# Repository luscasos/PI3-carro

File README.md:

# Projeto integrador III

## Informações gerais
Desenvolvido no escopo da disciplina de Projeto Integrador III, do curso de Eng. Eletrônica do IFSC campus Florianópolis no primeiro semestre de 2019, esse projeto tem como objetivo utilizar os conhecimentos obtidos ao decorrer do curso, implementando um carro controlado via aplicativo Android.

## Tabela inicial de requisitos
* Controle via aplicativo Android
* Comunicação via bluetooth
* Sensoriamento de velocidade e transmissão para o app 
* Controle de velocidade via aplicativo 
* Controle da bateria

## Tecnologias
* Parte mecânica do carro, disponível em https://s.click.aliexpress.com/e/bD9t0zL3
* Celular Android
* Microcontrolador STM32
* Bateria de íon de lítio
	
# Hardware

* ## Acionamento dos motores

Para acionar os motores foram levadas em conta os requisitos de projeto, que nesse quesito são:
* Controle de direção do movimento
* Controle de velocidade

Com relação ao controle de direção foi escolhido o sistema de ponte H, na qual é possível alterar o sentido da corrente invertendo as tensões nos terminais L e R, a forma escolhida de acionamento dos motores foi conectar em paralelo os motores do mesmo lado do carro, necessitando de duas pontes para o controle dos quatro motores 

O primeiro filtro para escolha do circuito foi a disponibilidade de componentes no almoxarifado, que para ponte H se limitava a:
* L293B
Corrente máxima 1A por canal

* L6203		
Corrente máxima 5A

* SN754410NE
Com uso restrito para manutenção

* Circuito discreto com BD140 e BD139
Corrente máxima 1,5A
 
### Escolha
Como nesse projeto vamos trabalhar com quatro motores, dois por canal, e sendo eles de tensão nominal de 3 - 6V e corrente nominal de 300mA todos os circuitos cumprem o requisito de potência mínima, O L6203 foi descartado por ser uma ponte H de potência, ficando superdimensionado e encarecendo o projeto, ficando a escolha entre o circuito discreto e o L2931B no quesito eficiência energética, afinal, se trata de um sistema embarcado, e por isso necessita de um cuidado maior com a eficiência
Montado os dois circuitos de acionamento alimentados em 5V foi obtido uma tensão de 3,08V com o integrado e 4,6V no circuito discreto, uma diferença de 35% no consumo do circuito, sendo escolhido o circuito discreto.  

Circuito final de alimentação dos motores, com queda de 0,4V de tensão na carga em relação a VCC e corrente de polarização externa de 640pA, não exigindo muita corrente do microcontrolador.

* ## Microcontrolador
Para controle do carro foi utilizado o stm32f103, na sua versão de desenvolvimento conhecido como "blue pill", que possui um cortex M3 com um clock de 72MHz e que conta com 20kb de RAM, quatro Timers, dois ADCs entre outros, que serão usados na aplicação.

* ## Comunicação
Como a comunicação entre celular e carro é feita via bluetooth foi escolhido o modulo HC-05, que trata todo o protocolo de comunicação e se comunica com microcontrolador via UART, sendo de fácil uso e configuração.

* ## Aferição de velocidade 
Para medir a velocidade foi escolhido um encoder com sensor óptico, que consiste em um diodo emissor de luz e um receptor, separados por uma roda perfurada, que quando a roda esta em movimento gera um sinal com frequência proporcional a velocidade da roda.

* ## Baterias 
Para alimentar o carro foram escolhidas duas baterias de LIPO, de 3,7V e 1200mAh, conectadas em série, o que resulta em 7,4V de tensão. 

* ## Regulador de tensão
Como o conjunto de baterias tem como tensão 7,4V na saída, é necessário baixar a tensão para níveis aceitáveis para o microcontrolador e modulo bluetooth, no caso foi usado um regulador ajustável Step-up-down, por questão de disponibilidade, mesmo esse sendo superdimensionado para a aplicação em questão, já que suporta correntes de até 5A e nesse caso não passa de 200mA.

* ## Medição da tensão das baterias
Como regra geral, não se pode descarregar uma bateria abaixo de uma certa tensão, com as usadas nesse projeto não é diferente, não sendo recomendado baixar a tensão da marca dos 3V, como o sistema possui duas baterias é necessário medir a tensão delas individualmente. O conversor analógico digital do microcontrolador tem como tensão base 3V, então é preciso baixar as tensões para menos de 3V, o circuito usado para isso é o diferencial com ampop, que pode dar um ganho menor que 1, sem usar tensão negativa. O Ampop escolhido foi o LM324, com ganho de 1/3 para a tensão superior (bateria 1 em serie com a bateria 2), e de 2/3 para a tensão media (bateria 1). 

* ## Placa de circuito
Com todos os requisitos de Hardware definidos foi desenvolvido o esquemático e placa do projeto

A placa de circuito impresso foi projetada para que o circuito de comunicação bluetooth ficasse longe do principal foco do ruído do circuito, que são os motores, contudo ainda foi deixado o uC ao lado dos motores e das pontes H, uma implementação mais correta seria distanciar esses dois componentes geradores de ruído, juntamente com o regulador de tensão. e acoplar o sensor de velocidade de outra maneira, que não por cabos longos como foi projetado, essas e outras correções foram feitas em outra placa a ser utilizada em disciplinas ligadas a programação de microcontroladores.

O carro também foi objeto de estudo por uma dupla de colegas dentro da disciplina de compatibilidade eletromagnética, estando todos dados disponíveis no link https://github.com/lsmanoel/CEM_3

# Software do microcontrolador

* ## Controle de velocidade
O controle da velocidade vai ser feito por meio da técnica de modulação PWM, via microcontrolador atuando sobre a ponte H.
Como o circuito de ponte H escolhido não pode em hipótese alguma ter o os dois transistores de atuação polarizados ao mesmo tempo, optou-se por utilizar o PWM no modo normal e no modo inverso, de forma a construir um sistema redundante nesse sentido, se houver uma falha no software mesmo assim não haverá um problema critico na ponte H.

A implementação foi feita via dois Timers, com frequência fixa em 1kHz, em ambos usando o canal 1 e o canal 1N, trabalhando sempre com pelo menos um deles desligado. Sabendo que a velocidade vai ser transmitida pelo aplicativo em 1Byte, com 256 possibilidades, de -128 a 127. Sendo assim o valor 127 corresponde a 100% da velocidade para frente, enquanto -128 corresponde a 100% da velocidade na ré.
Como os motores possuem uma inércia, não será qualquer valor de tensão que dará partida no carro, sabendo disso pode-se dar um offset no valor do pwm, nesse caso escolhi cerca de 45% de razão cíclica, o que é suficiente para dar partida nos motores.

* ## Medição das baterias
A medição das baterias foi feita por um ADC, utilizando dois canais, um para a tensão total (bateria 1 em serie com a bateria 2) e um canal para a tensão da bateria 1, lembrando que estas tensões já receberam um ganho de 1/3 (tensão total) e 2/3 (tensão da bateria 1). então levando em consideração esse ganho e os dois canais pode-se medir individualmente a tensão de cada bateria para que o sistema possa desligar os motores e avisar o usuário que a carga das baterias esta crítica.

* ## Medição da velocidade
A velocidade é calculada com base na variação de um sensor ótico e como a roda perfurada possui 20 furos, para cada uma volta da roda são medidas 20 alternâncias no sensor, com isso e o diâmetro da roda é possível saber a distância percorrida por pulso. Além da componente de distância é necessário saber o tempo entre medições, nesse caso foi utilizada um tempo de 100ms.

onde n é o número de pulsos por período

Também foi implementado um [filtro media movel](http://borgescorporation.blogspot.com/2013/05/filtro-de-media-movel.html
) de 16 fatores afim de filtrar ruídos indesejados

* ## Comunicação
A comunicação entre o microcontrolador e o modulo bluetooth HC-05 é feita via UART que possui hardware dedicado na maioria dos microcontroladores, então a implementação consiste basicamente em criar um pacote de dados para envio de todos os parâmetros juntos no formato "00;00;00;00". O tratamento de dados recebidos pelo uC é feito por interrupção, reconhecendo o final do dado, que é "\r\n" e separando os demais bits, que são as coordenadas Y e Z.

# Controle de Direção e sentido
Tanto o controle de direção quanto o de sentido serão feitas via aplicação em Android e transmitidas por bluetooth para o microcontrolador embarcado no carro, o controle de sentido será feito via dois botões, um para ré e outro para frente, não pressionado nenhum o carro fica parado, com a possibilidade de fixar uma velocidade constante. A direção será feita via medição dos acelerômetros do celular, que fara o celular nesse caso atuar como um volante.

# Aplicativo Android

O aplicativo conta com as seguintes funcionalidades:

* Botão de conexão bluetooth no canto superior direito, que é responsável por ligar o bluetooth caso o mesmo esteja desligado, buscar a lista de dispositivos pareados e conectar no mesmo, iniciando a comunicação.
* Botão Start/Stop responsável por interromper ou não o fluxo de dados de aceleração do celular para o dispositivo pareado.
* Texto central com os valores de aceleração individual dos eixos.
* Texto na lateral esquerda com os valores de bateria e velocidade enviados pelo dispositivo conectado. 

<p>
A estrutura dos dados de aceleração é a seguinte: 
<pre><code>byte dado[]=new byte[4];
        dado[0]=y;
        dado[1]=z;
        dado[2]='\r';
        dado[3]='\n';
        connectedThread.write(dado);
  </code></pre>
</p>

Já a estrutura dos dados recebidos tem que estar no seguinte formato: "00;00;00;00", sendo que o aplicativo insere uma virgula entre cada um dos valores.

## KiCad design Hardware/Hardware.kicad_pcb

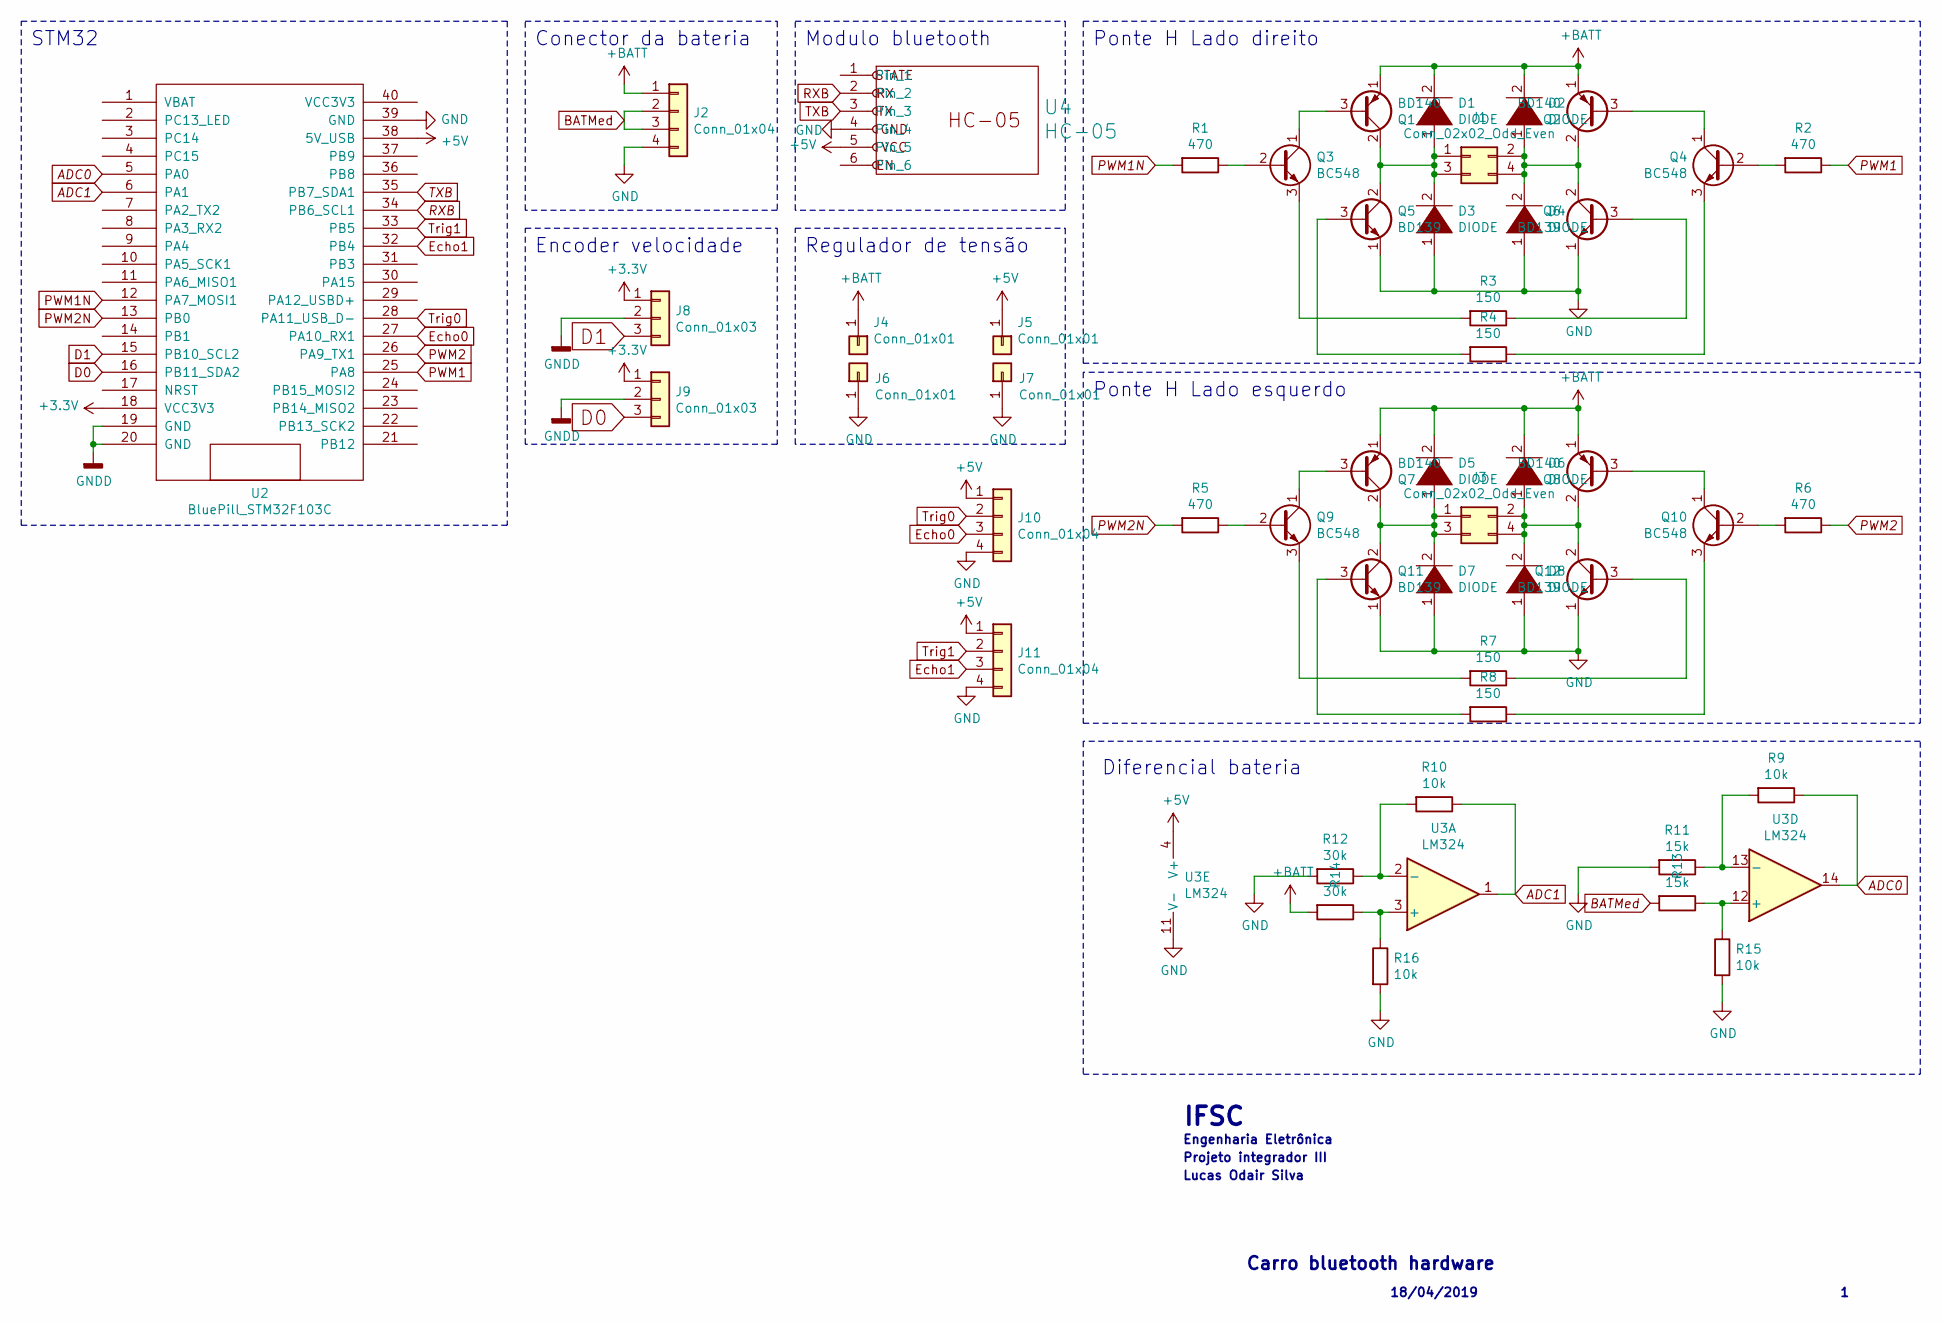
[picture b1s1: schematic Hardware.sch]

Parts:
D1, D2, D3, D4, D5, D6, D7, D8: DIODE; D_A-405_P2.54mm_Vertical_AnodeUp
J1, J3: Conn_02x02_Odd_Even; PinHeader_2x02_P2.54mm_Vertical
J2, J10, J11: Conn_01x04; PinHeader_1x04_P2.54mm_Vertical
J4, J5, J6, J7: Conn_01x01; PinHeader_1x01_P2.54mm_Vertical
J8, J9: Conn_01x03; PinHeader_1x03_P2.54mm_Vertical
Q1, Q2, Q7, Q8: BD140; TO-126-3_Vertical
Q3, Q4, Q9, Q10: BC548; TO-92_Inline
Q5, Q6, Q11, Q12: BD139; TO-126-3_Vertical
R1, R2, R5, R6: 470; R_0805_2012Metric
R3, R4, R7, R8: 150; R_0805_2012Metric
R9, R10, R15, R16: 10k; R_0805_2012Metric
R11, R13: 15k; R_0805_2012Metric
R12, R14: 30k; R_0805_2012Metric
U2: BluePill_STM32F103C
U3: LM324; SOIC-14_3.9x8.7mm_P1.27mm
U4: HC-05; PinHeader_1x06_P2.54mm_Horizontal

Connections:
+3V3: J8.1, J9.1, U2.18 (VCC3V3)
+5V: J5.1, J10.1, J11.1, U2.38 (5V_USB), U3.4 (V+), U4.5
+BATT: D1.2 (A), D2.2 (A), D5.2 (A), D6.2 (A), J2.1, J4.1, Q1.1 (E), Q2.1 (E), Q7.1 (E), Q8.1 (E), R14.2
ADC0: R9.1, U2.5 (PA0), U3.14
ADC1: R10.1, U2.6 (PA1), U3.1
BATMed: J2.2, J2.3, R13.2
D0: J9.3, U2.16 (PB11_SDA2)
D1: J8.3, U2.15 (PB10_SCL2)
Echo0: J10.3, U2.27 (PA10_RX1)
Echo1: J11.3, U2.32 (PB4)
GND: D3.1 (K), D4.1 (K), D7.1 (K), D8.1 (K), J2.4, J6.1, J7.1, J10.4, J11.4, Q5.1 (E), Q6.1 (E), Q11.1 (E), Q12.1 (E), R11.2, R12.2, R15.2, R16.2, U2.39 (GND), U3.11 (V-), U4.4
GNDD: J8.2, J9.2, U2.19 (GND), U2.20 (GND)
unnamed: D1.1 (K), D3.2 (A), J1.1, J1.3, Q1.2 (C), Q5.2 (C)
unnamed: D2.1 (K), D4.2 (A), J1.2, J1.4, Q2.2 (C), Q6.2 (C)
unnamed: D5.1 (K), D7.2 (A), J3.1, J3.3, Q7.2 (C), Q11.2 (C)
unnamed: D6.1 (K), D8.2 (A), J3.2, J3.4, Q8.2 (C), Q12.2 (C)
unnamed: Q1.3 (B), Q3.1 (C)
unnamed: Q2.3 (B), Q4.1 (C)
unnamed: Q3.2 (B), R1.1
unnamed: Q3.3 (E), R3.2
unnamed: Q4.2 (B), R2.2
unnamed: Q4.3 (E), R4.1
unnamed: Q5.3 (B), R4.2
unnamed: Q6.3 (B), R3.1
unnamed: Q7.3 (B), Q9.1 (C)
unnamed: Q9.2 (B), R5.1
unnamed: Q9.3 (E), R7.2
unnamed: Q8.3 (B), Q10.1 (C)
unnamed: Q10.2 (B), R6.2
unnamed: Q10.3 (E), R8.1
unnamed: Q11.3 (B), R8.2
unnamed: Q12.3 (B), R7.1
unnamed: R10.2, R12.1, U3.2 (-)
unnamed: R9.2, R11.1, U3.13 (-)
unnamed: R13.1, R15.1, U3.12 (+)
unnamed: R14.1, R16.1, U3.3 (+)
PWM1: R2.1, U2.25 (PA8)
PWM1N: R1.2, U2.12 (PA7_MOSI1)
PWM2: R6.1, U2.26 (PA9_TX1)
PWM2N: R5.2, U2.13 (PB0)
RXB: U2.34 (PB6_SCL1), U4.2
TXB: U2.35 (PB7_SDA1), U4.3
Trig0: J10.2, U2.28 (PA11_USB_D-)
Trig1: J11.2, U2.33 (PB5)

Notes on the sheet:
Carro bluetooth hardware
18/04/2019
IFSC
Projeto integrador III
Lucas Odair Silva
Engenharia Eletrônica
Ponte H Lado direito
Ponte H Lado esquerdo
Diferencial bateria
Modulo bluetooth
Conector da bateria
Regulador de tensão
STM32
Encoder velocidade

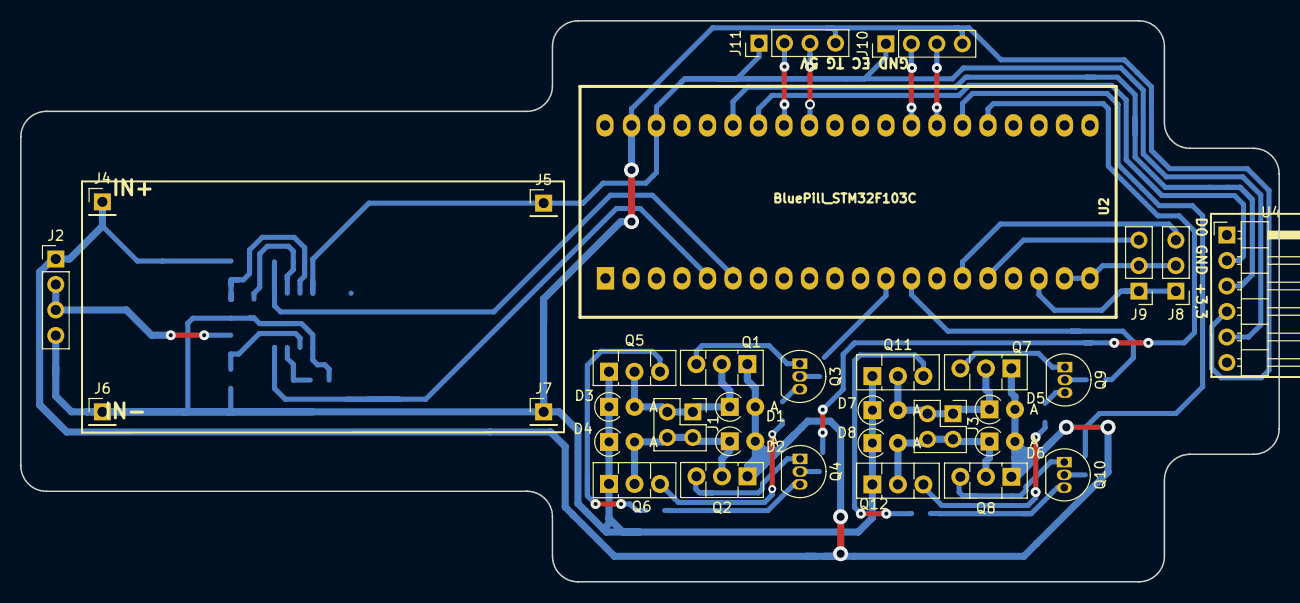
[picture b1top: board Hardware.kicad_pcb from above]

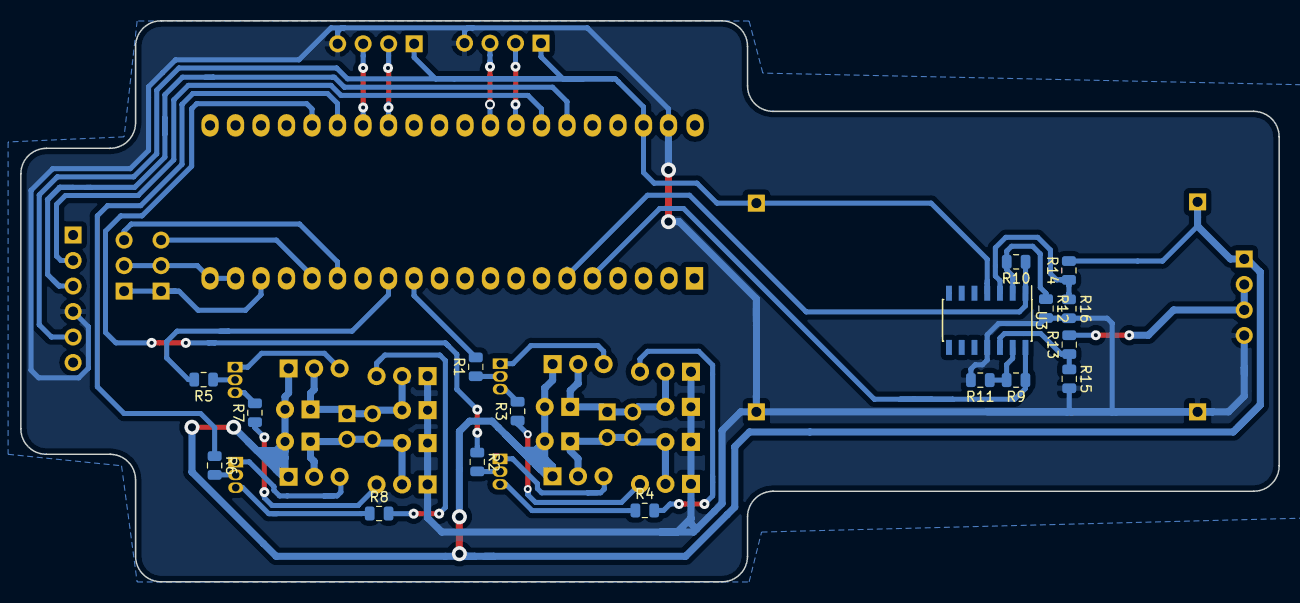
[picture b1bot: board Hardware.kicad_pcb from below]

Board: 2 copper layers, 125.3 x 55.9 mm, 50 parts (17 on the bottom side), 44 nets.

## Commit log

2019-04-19 esquematico kicac
    adicionado o projeto do hardware no kicad
    atualizado o app e projeto do ucontrolador
